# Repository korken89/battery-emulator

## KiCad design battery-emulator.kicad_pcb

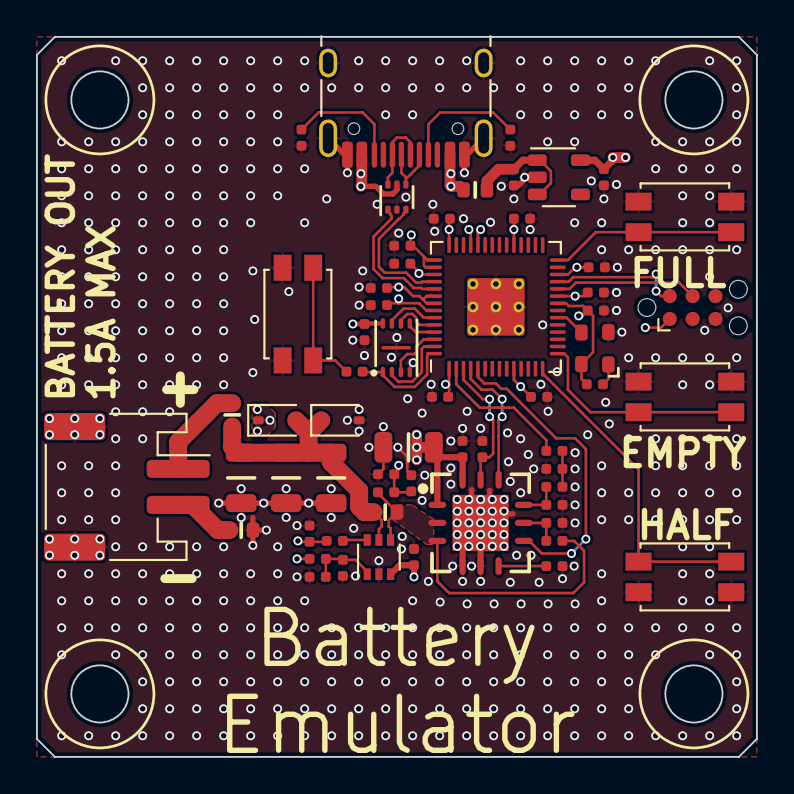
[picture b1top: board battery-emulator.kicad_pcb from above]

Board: 4 copper layers, 40.0 x 40.0 mm, 60 parts (0 on the bottom side), 41 nets.

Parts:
C1: 47u; C_1206
C2, C3, C5, C9, C10, C11, C12, C13, C14, C15, C16, C17, C20, C21, C22, C25: 0.1u; C_0402
C4, C23, C24: 100u; C_1206
C6, C7, C8, C18, C19: 2.2u; C_0402
D1, D2: 1A, 40V; D_SOD-323
FB1, FB2, FB3: BLM18KG471SN1D; R_0603
J1: USB_C_Receptacle_USB2.0; USB_C_Receptacle_USB4105
J2: tag-connect-swd; Tag-Connect_TC2030-IDC-NL_2x03_P1.27mm_Vertical
J3: FakeBattery; JST_PH_S2B-PH-SM4-TB_1x02-1MP_P2.00mm_Horizontal
R1, R2, R9, R10, R11, R12, R13, R14: 10k; R_0402
R3: 20m; R_0603
R4, R5: 5.1k; R_0402
R6, R7: 1k; R_0402
R8: 7.68k; R_0402
R15, R16: 100k; R_0402
SW1, SW2, SW3, SW4: SW_Push; SW_SPST_EVQP2
U1: OPA567AIRHGR; PVQFN-N12-1EP_5.0x5.0mm_P1.0mm_EP3.12x3.12mm
U2: INA199A1DCKR; SOT-363_SC-70-6
U3: NUF2042XV6T1G; SOT-563
U4: W25Q8; USON-8-3x2mm-EP
U5: RP2040; RP2040-QFN-56
U6: NCP161ASN330T1G; SOT-23-5
X1: 12 MHz; Crystal_SMD_2520-4Pin_2.5x2.0mm

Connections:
+1V1: C7.1, C9.1, C11.1, U5.23 (DVDD), U5.45 (VREG_VOUT), U5.50 (DVDD)
+3.3V: C3.1, C5.1, C6.1, C8.1, C10.1, C12.1, C13.1, C14.1, C15.1, C16.1, C19.1, J2.1 (VCC), R6.1, R9.2, U2.3 (V+), U4.8 (VCC), U5.1 (IOVDD), U5.10 (IOVDD), U5.22 (IOVDD), U5.26 (RUN), U5.33 (IOVDD), U5.42 (IOVDD), U5.43 (ADC_AVDD), U5.44 (VREG_IN), U5.48 (USB_VDD), U5.49 (IOVDD), U6.5 (VOUT), X1.4 (VDD)
+5V: C1.1, C2.1, D1.1 (K), FB3.1, J1.A4 (VBUS), J1.A9 (VBUS), J1.B4 (VBUS), J1.B9 (VBUS), U1.1 (V+), U1.12 (V+), U3.5 (VBUS)
/CURR0: U1.7 (I_{FLAG}), U5.5 (GPIO3)
/D_FS_N: U3.3 (D2I), U5.46 (USB_DM)
/D_FS_P: U3.1 (D1I), U5.47 (USB_DP)
/D_N: J1.A7 (D-), J1.B7 (D-), U3.4 (D2O)
/D_P: J1.A6 (D+), J1.B6 (D+), U3.6 (D1O)
/ENABLE0: R11.2, U1.11 (ENABLE), U5.3 (GPIO1)
/IMEAS_0: C22.1, R14.1, U5.38 (GPIO26_ADC0)
/P_SWCLK: J2.4 (SWCLK), U5.24 (SWCLK)
/P_SWDIO: J2.2 (SWDIO), U5.25 (SWD)
/Power stage/IN+: C21.1, R13.2, U1.9 (IN+)
/Power stage/IN-: R1.2, R2.1, U1.8 (IN-)
/Power stage/I_{MEAS,REF}: C17.1, R9.1, R10.2, U2.1 (REF)
/Power stage/V_{O,PROT}: C4.1, C23.1, C24.1, D1.2 (A), D2.1 (K), FB1.1, R3.2, U2.5 (-)
/Power stage/V_{O}: R2.2, R3.1, R15.2, U1.2 (V_{O}), U1.3 (V_{O}), U2.4 (+)
/SW1: SW2.2, U5.28 (GPIO17)
/SW2: SW3.2, U5.14 (GPIO11)
/SW3: SW4.2, U5.15 (GPIO12)
/TEMP0: U1.10 (T_{FLAG}), U5.4 (GPIO2)
/VMEAS_0: C25.1, R15.1, R16.2, U5.39 (GPIO27_ADC1)
/VREF_0: R12.1, U5.2 (GPIO0)
/XIN: U5.20 (XIN), X1.3 (OUT)
GND: C1.2, C2.2, C3.2, C4.2, C5.2, C6.2, C7.2, C8.2, C9.2, C10.2, C11.2, C12.2, C13.2, C14.2, C15.2, C16.2, C17.2, C18.2, C19.2, C20.2, C21.2, C22.2, C23.2, C24.2, C25.2, D2.2 (A), FB2.1, J1.A1 (GND), J1.A12 (GND), J1.B1 (GND), J1.B12 (GND), J1.S1 (SHIELD), J2.5 (GND), J3.MP (MountPin), R1.1, R4.2, R5.2, R8.1, R10.1, R11.1, R16.1, SW1.1, SW2.1, SW3.1, SW4.1, U1.4 (V-), U1.5 (V-), U1.13 (V-), U2.2 (GND), U3.2 (GND), U4.4 (GND), U4.9 (EP), U5.19 (TESTEN), U5.57 (GND), U6.2 (GND), X1.2 (GND)
unnamed: C20.1, R12.2, R13.1
unnamed: J1.A5 (CC1), R4.1
unnamed: J1.B5 (CC2), R5.1
unnamed: FB1.2, J3.1
unnamed: FB2.2, J3.2
unnamed: R7.2, SW1.2
unnamed: R14.2, U2.6
unnamed: R8.2, U1.6 (I_{SET})
unnamed: U4.6 (CLK), U5.52 (QSPI_SCLK)
unnamed: U4.5 (DI(IO0)), U5.53 (QSPI_SD0)
unnamed: U4.2 (DO(IO1)), U5.55 (QSPI_SD1)
unnamed: U4.3 (IO2), U5.54 (QSPI_SD2)
unnamed: U4.7 (IO3), U5.51 (QSPI_SD3)
unnamed: R7.1, U4.1 (~CS), U5.56 (QSPI_SS)
unnamed: C18.1, FB3.2, U6.1 (VIN), U6.3 (EN)
unnamed: R6.2, X1.1 (Tri-State)

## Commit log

2023-06-03 Added OPA567
2023-06-03 Started designing
2023-06-04 Some design
2023-06-04 More layout
2023-06-06 Layout complete
2023-06-18 More fixes
